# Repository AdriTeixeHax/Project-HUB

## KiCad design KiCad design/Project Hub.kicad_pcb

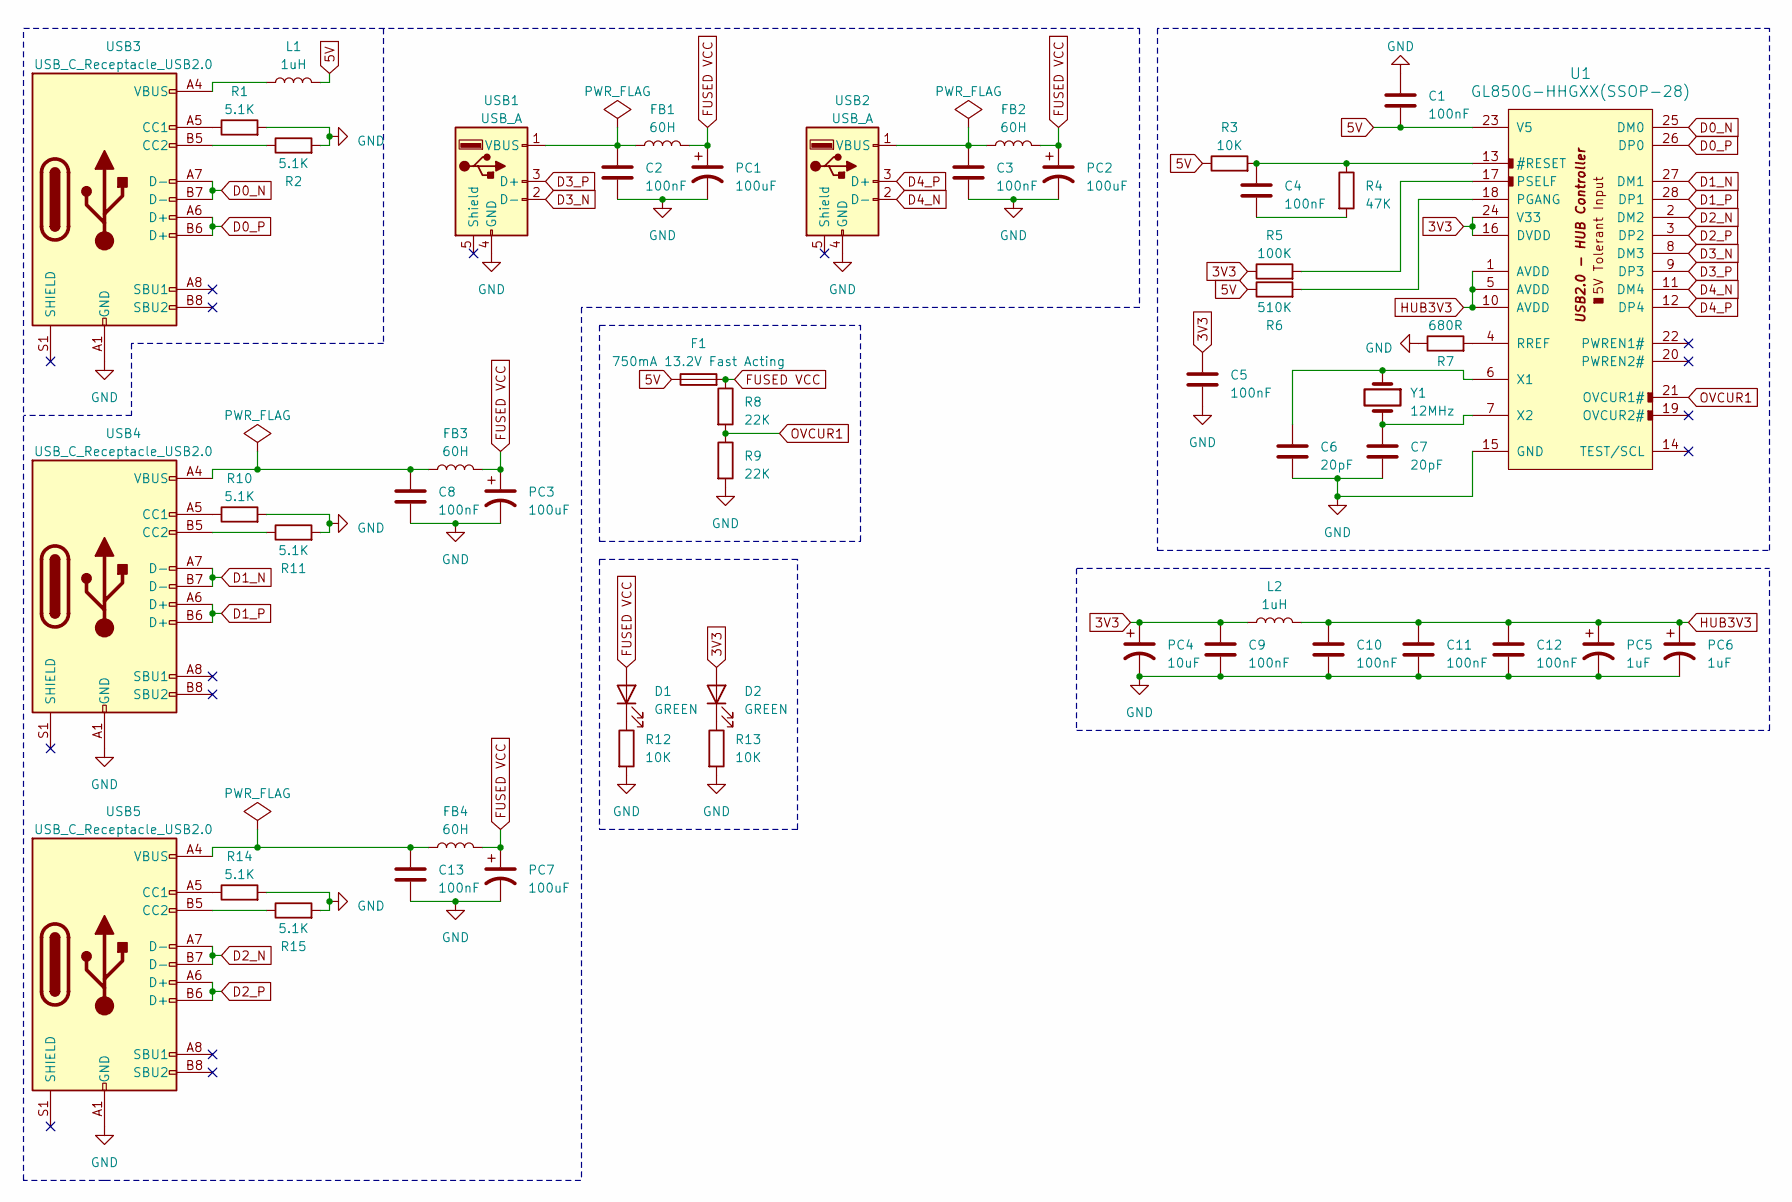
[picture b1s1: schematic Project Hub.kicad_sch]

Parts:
C1, C2, C3, C4, C5, C8, C9, C10, C11, C12, C13: 100nF; C_0603_1608Metric
C6, C7: 20pF; C_0603_1608Metric
D1, D2: GREEN; LED_0805_2012Metric
F1: 750mA 13.2V Fast Acting; Fuse_1812_4532Metric
FB1, FB2, FB3, FB4: 60H; L_0805_2012Metric
L1, L2: 1uH; L_0805_2012Metric
PC1, PC2, PC3, PC7: 100uF; CP_Radial_D5.0mm_P2.00mm
PC4: 10uF; CP_Radial_D5.0mm_P2.00mm
PC5, PC6: 1uF; CP_Radial_D5.0mm_P2.00mm
R1, R2, R10, R11, R14, R15: 5.1K; R_0603_1608Metric
R3, R12, R13: 10K; R_0603_1608Metric
R4: 47K; R_0603_1608Metric
R5: 100K; R_0603_1608Metric
R6: 510K; R_0603_1608Metric
R7: 680R; R_0603_1608Metric
R8, R9: 22K; R_0603_1608Metric
U1: GL850G-HHGXX(SSOP-28); SSOP-28_5.3x10.2mm_P0.65mm
USB1, USB2: USB_A; USB_A_Molex_67643_Horizontal
USB3, USB4, USB5: USB_C_Receptacle_USB2.0; USB_C_Receptacle_Palconn_UTC16-G
Y1: 12MHz; Crystal_HC50_Vertical

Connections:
3V3: C5.1, C9.1, D2.2 (A), L2.1, PC4.1, R5.1, U1.16 (DVDD), U1.24 (V33)
5V: C1.2, F1.1, L1.2, R3.1, R6.1, U1.23 (V5)
D0_N: U1.25 (DM0), USB3.A7 (D-), USB3.B7 (D-)
D0_P: U1.26 (DP0), USB3.A6 (D+), USB3.B6 (D+)
D1_N: U1.27 (DM1), USB4.A7 (D-), USB4.B7 (D-)
D1_P: U1.28 (DP1), USB4.A6 (D+), USB4.B6 (D+)
D2_N: U1.2 (DM2), USB5.A7 (D-), USB5.B7 (D-)
D2_P: U1.3 (DP2), USB5.A6 (D+), USB5.B6 (D+)
D3_N: U1.8 (DM3), USB1.2 (D-)
D3_P: U1.9 (DP3), USB1.3 (D+)
D4_N: U1.11 (DM4), USB2.2 (D-)
D4_P: U1.12 (DP4), USB2.3 (D+)
FUSED VCC: D1.2 (A), F1.2, FB1.2, FB2.2, FB3.2, FB4.2, PC1.1, PC2.1, PC3.1, PC7.1, R8.1
GND: C1.1, C2.2, C3.2, C5.2, C6.2, C7.2, C8.2, C9.2, C10.2, C11.2, C12.2, C13.2, PC1.2, PC2.2, PC3.2, PC4.2, PC5.2, PC6.2, PC7.2, R1.2, R2.2, R7.1, R9.2, R10.2, R11.2, R12.2, R13.2, R14.2, R15.2, U1.15 (GND), USB1.4 (GND), USB2.4 (GND), USB3.A1 (GND), USB3.A12 (GND), USB3.B1 (GND), USB3.B12 (GND), USB4.A1 (GND), USB4.A12 (GND), USB4.B1 (GND), USB4.B12 (GND), USB5.A1 (GND), USB5.A12 (GND), USB5.B1 (GND), USB5.B12 (GND)
HUB3V3: C10.1, C11.1, C12.1, L2.2, PC5.1, PC6.1, U1.1 (AVDD), U1.5 (AVDD), U1.10 (AVDD)
unnamed: C4.2, R4.2
unnamed: C8.1, FB3.1, USB4.A4 (VBUS), USB4.A9 (VBUS), USB4.B4 (VBUS), USB4.B9 (VBUS)
unnamed: C13.1, FB4.1, USB5.A4 (VBUS), USB5.A9 (VBUS), USB5.B4 (VBUS), USB5.B9 (VBUS)
unnamed: D1.1 (K), R12.1
unnamed: D2.1 (K), R13.1
unnamed: L1.1, USB3.A4 (VBUS), USB3.A9 (VBUS), USB3.B4 (VBUS), USB3.B9 (VBUS)
unnamed: C4.1, R3.2, R4.1, U1.13 (#RESET)
unnamed: R6.2, U1.18 (PGANG)
unnamed: R5.2, U1.17 (PSELF)
unnamed: R7.2, U1.4 (RREF)
unnamed: C6.1, U1.6 (X1), Y1.1
unnamed: C7.1, U1.7 (X2), Y1.2
unnamed: C2.1, FB1.1, USB1.1 (VBUS)
unnamed: C3.1, FB2.1, USB2.1 (VBUS)
unnamed: R1.1, USB3.A5 (CC1)
unnamed: R2.1, USB3.B5 (CC2)
unnamed: R10.1, USB4.A5 (CC1)
unnamed: R11.1, USB4.B5 (CC2)
unnamed: R14.1, USB5.A5 (CC1)
unnamed: R15.1, USB5.B5 (CC2)
OVCUR1: R8.2, R9.1, U1.21 (OVCUR1#)

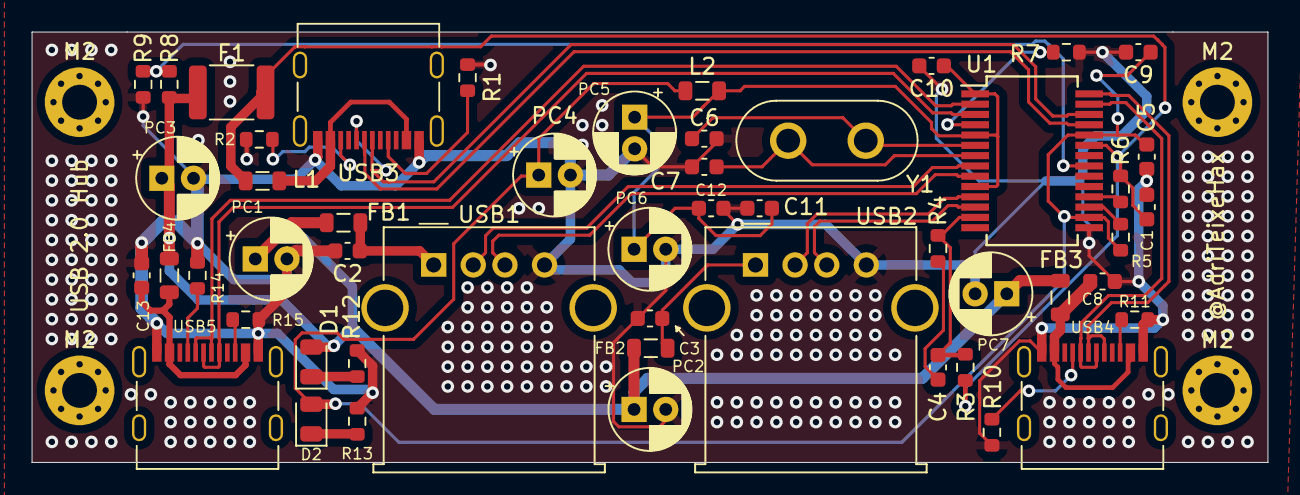
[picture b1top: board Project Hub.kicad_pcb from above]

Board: 2 copper layers, 78.0 x 27.2 mm, 55 parts (0 on the bottom side), 36 nets.

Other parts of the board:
M2, M2#2, M2#3, M2#4: MountingHole_2.2mm_M2_Pad_Via

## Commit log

2025-03-31 fixed upstream port 5.1k resistors
